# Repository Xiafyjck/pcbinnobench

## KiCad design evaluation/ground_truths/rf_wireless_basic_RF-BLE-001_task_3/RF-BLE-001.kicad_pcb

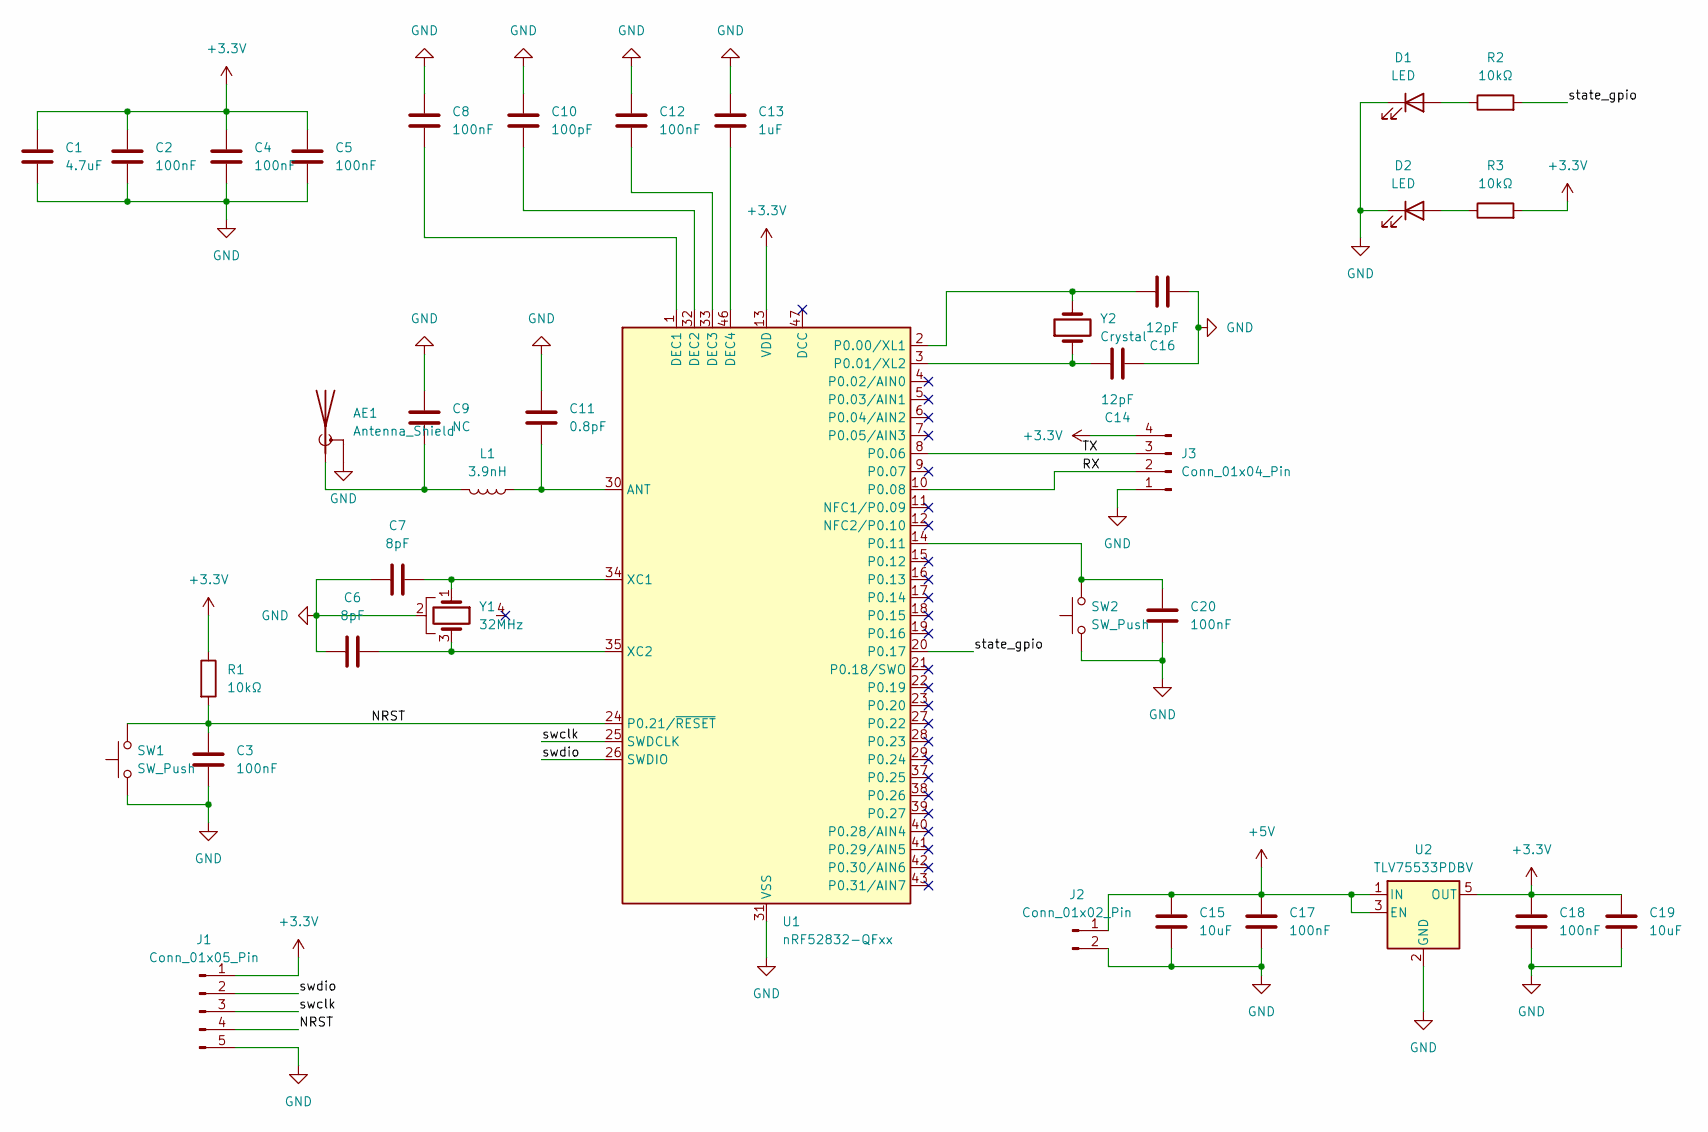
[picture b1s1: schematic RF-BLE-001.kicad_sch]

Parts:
AE1: Antenna_Shield; Texas_SWRA117D_2.4GHz_Right
C1: 4.7uF; C_0805_2012Metric
C2, C3, C4, C5, C8, C12, C17, C18, C20: 100nF; C_0805_2012Metric
C6, C7: 8pF; C_0805_2012Metric
C9: NC; C_0402_1005Metric
C10: 100pF; C_0805_2012Metric
C11: 0.8pF; C_0402_1005Metric
C13: 1uF; C_0805_2012Metric
C14, C16: 12pF; C_0805_2012Metric
C15, C19: 10uF; C_0805_2012Metric
D1, D2: LED; LED_0805_2012Metric
J1: Conn_01x05_Pin; JST_XH_B5B-XH-A_1x05_P2.50mm_Vertical
J2: Conn_01x02_Pin; JST_EH_B2B-EH-A_1x02_P2.50mm_Vertical
J3: Conn_01x04_Pin; JST_XH_B4B-XH-A_1x04_P2.50mm_Vertical
L1: 3.9nH; C_0402_1005Metric
R1, R2, R3: 10kΩ; R_0805_2012Metric
SW1, SW2: SW_Push; SW_PUSH_6mm
U1: nRF52832-QFxx; QFN-48-1EP_6x6mm_P0.4mm_EP4.6x4.6mm
U2: TLV75533PDBV; SOT-23-5
Y1: 32MHz; Crystal_SMD_Abracon_ABM8AIG-4Pin_3.2x2.5mm
Y2: Crystal; Crystal_HC49-4H_Vertical

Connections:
+3.3V: C1.1, C2.1, C4.1, C5.1, C18.1, C19.1, J1.1, J3.4, R1.1, R3.2, U1.13 (VDD), U1.36 (VDD), U1.48 (VDD), U2.5 (OUT)
+5V: C15.1, C17.1, J2.1, U2.1 (IN), U2.3 (EN)
/NRST: C3.1, J1.4, R1.2, SW1.2, U1.24 (P0.21/~RESET)
/RX: J3.2, U1.10 (P0.08)
/TX: J3.3, U1.8 (P0.06)
/state_gpio: R2.2, U1.20 (P0.17)
/swclk: J1.3, U1.25 (SWDCLK)
/swdio: J1.2, U1.26 (SWDIO)
GND: AE1.2 (Shield), C1.2, C2.2, C3.2, C4.2, C5.2, C6.1, C7.1, C8.1, C9.1, C10.1, C11.1, C12.1, C13.1, C14.1, C15.2, C16.1, C17.2, C18.2, C19.2, C20.2, D1.1 (K), D2.1 (K), J1.5, J2.2, J3.1, SW1.1, SW2.1, U1.31 (VSS), U1.45 (VSS), U1.49 (VSS), U2.2 (GND), Y1.2
unnamed: AE1.1 (A), C9.2, L1.2
unnamed: D1.2 (A), R2.1
unnamed: D2.2 (A), R3.1
unnamed: C11.2, L1.1, U1.30 (ANT)
unnamed: C8.2, U1.1 (DEC1)
unnamed: C10.2, U1.32 (DEC2)
unnamed: C12.2, U1.33 (DEC3)
unnamed: C13.2, U1.46 (DEC4)
unnamed: C16.2, U1.2 (P0.00/XL1), Y2.2
unnamed: C14.2, U1.3 (P0.01/XL2), Y2.1
unnamed: C20.1, SW2.2, U1.14 (P0.11)
unnamed: C7.2, U1.34 (XC1), Y1.1
unnamed: C6.2, U1.35 (XC2), Y1.3

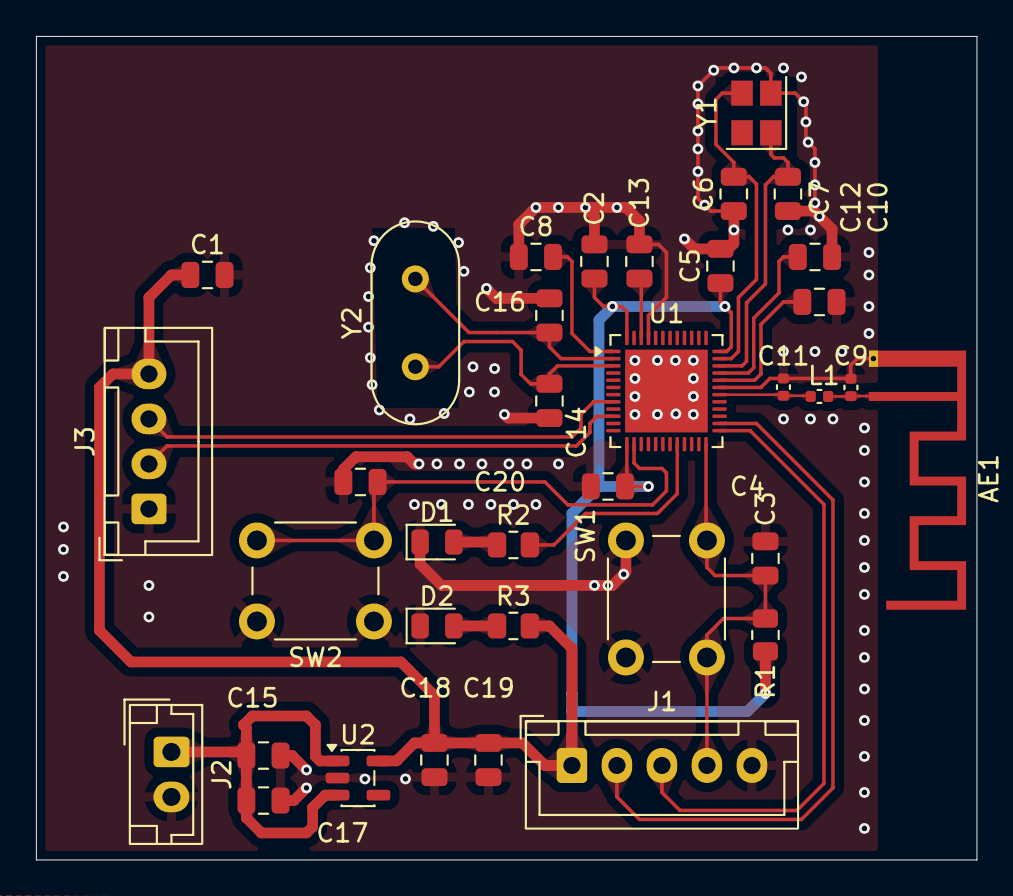
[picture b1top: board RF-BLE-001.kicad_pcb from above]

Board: 4 copper layers, 52.2 x 45.8 mm, 36 parts (0 on the bottom side), 22 nets.

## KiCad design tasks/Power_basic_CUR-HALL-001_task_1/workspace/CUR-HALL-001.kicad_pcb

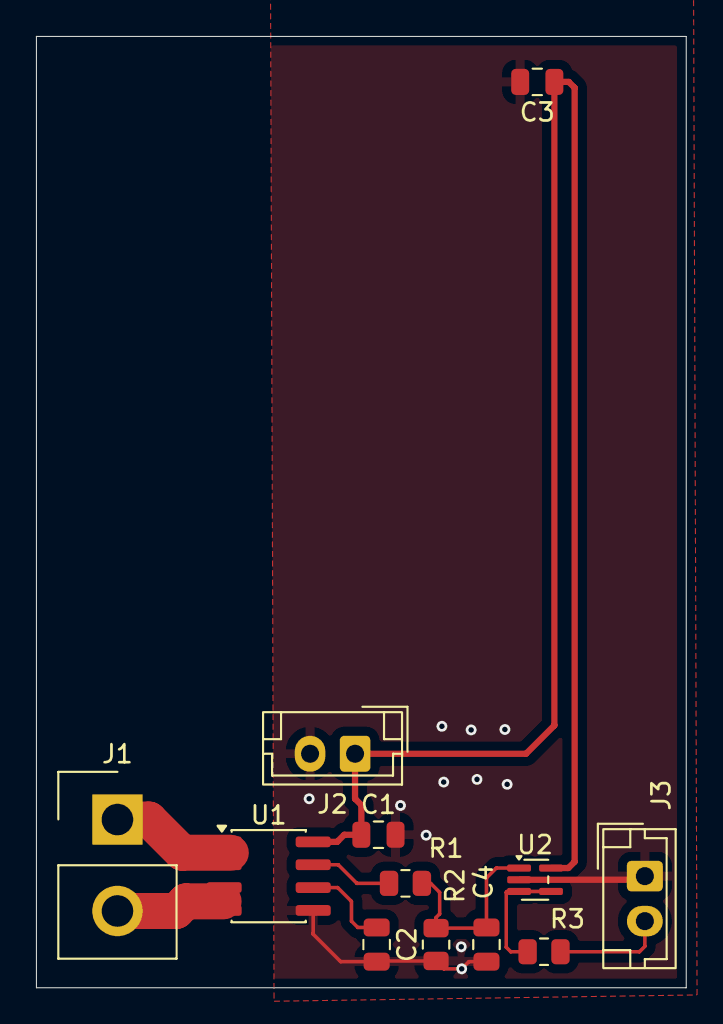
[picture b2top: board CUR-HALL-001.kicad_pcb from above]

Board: 2 copper layers, 36.1 x 52.9 mm, 12 parts (0 on the bottom side), 9 nets.

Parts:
C1, C3: 100nF; C_0805_2012Metric
C2, C4: 10nF; C_0805_2012Metric
J1: Conn_01x02_Pin; Samtec_HPM-02-01-x-S_Straight_1x02_Pitch5.08mm
J2, J3: Conn_01x02_Pin; JST_EH_B2B-EH-A_1x02_P2.50mm_Vertical
R1: 12kΩ; R_0805_2012Metric
R2: 22kΩ; R_0805_2012Metric
R3: 10Ω; R_0805_2012Metric
U1: ACS712xLCTR-20A; SOIC-8_3.9x4.9mm_P1.27mm
U2: OPA333xxDCK; SOT-353_SC-70-5

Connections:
+5V: C1.1, C3.1, J2.1, U1.8 (VCC), U2.5 (V+)
GND: C1.2, C2.2, C3.2, C4.2, J2.2, J3.1, R2.1, U1.5 (GND), U2.2 (V-)
unnamed: J1.1, U1.1 (IP+), U1.2 (IP+)
unnamed: J1.2, U1.3 (IP-), U1.4 (IP-)
unnamed: J3.2, R3.1
unnamed: C2.1, U1.6 (FILTER)
unnamed: R1.1, U1.7 (VIOUT)
unnamed: C4.1, R1.2, R2.2, U2.1 (+)
unnamed: R3.2, U2.3 (-), U2.4

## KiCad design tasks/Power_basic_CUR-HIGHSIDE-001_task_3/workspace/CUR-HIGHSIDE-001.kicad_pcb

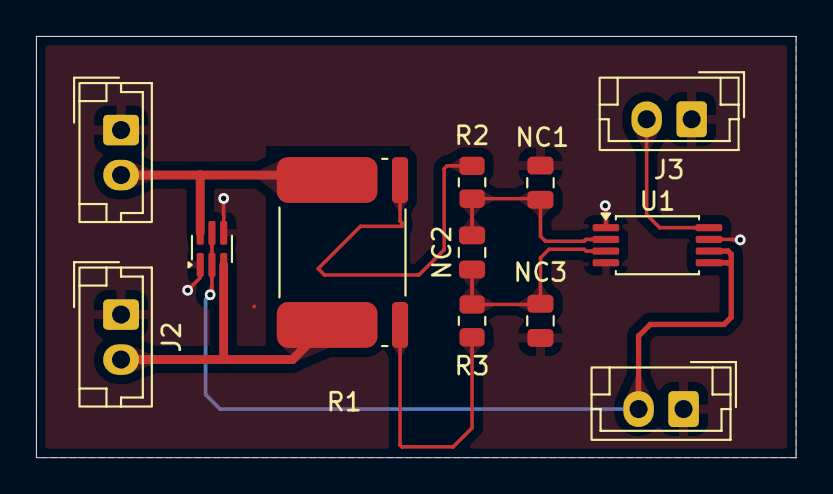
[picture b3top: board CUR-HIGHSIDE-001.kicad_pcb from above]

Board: 2 copper layers, 42.2 x 23.4 mm, 12 parts (0 on the bottom side), 9 nets.

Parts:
D1: BAV199DW; SOT-363_SC-70-6
J1, J2, J3, J4: Conn_01x02_Pin; JST_EH_B2B-EH-A_1x02_P2.50mm_Vertical
NC1: C1; C_0805_2012Metric
NC2: C2; C_0805_2012Metric
NC3: C3; C_0805_2012Metric
R1: 10mΩ; R_Shunt_Isabellenhuette_BVR4026
R2, R3: 0; R_0805_2012Metric
U1: INA240A1PW; TSSOP-8_4.4x3mm_P0.65mm

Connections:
+3V3: D1.2 (K2), D1.5 (K4), J4.2, U1.5 (V+), U1.6 (REF2)
/IN+: D1.6 (K3A4), J1.2, R1.4
/IN-: D1.3 (K1A2), J2.2, R1.1
/OUT: J3.2, U1.8
GND: D1.1 (A1), D1.4 (A3), J1.1, J2.1, J3.1, J4.1, NC1.2, NC3.1, U1.1 (GND), U1.4 (GND), U1.7 (REF1)
unnamed: R1.2, R3.2
unnamed: R1.3, R2.2
unnamed: NC1.1, NC2.2, R2.1, U1.2 (+)
unnamed: NC2.1, NC3.2, R3.1, U1.3 (-)

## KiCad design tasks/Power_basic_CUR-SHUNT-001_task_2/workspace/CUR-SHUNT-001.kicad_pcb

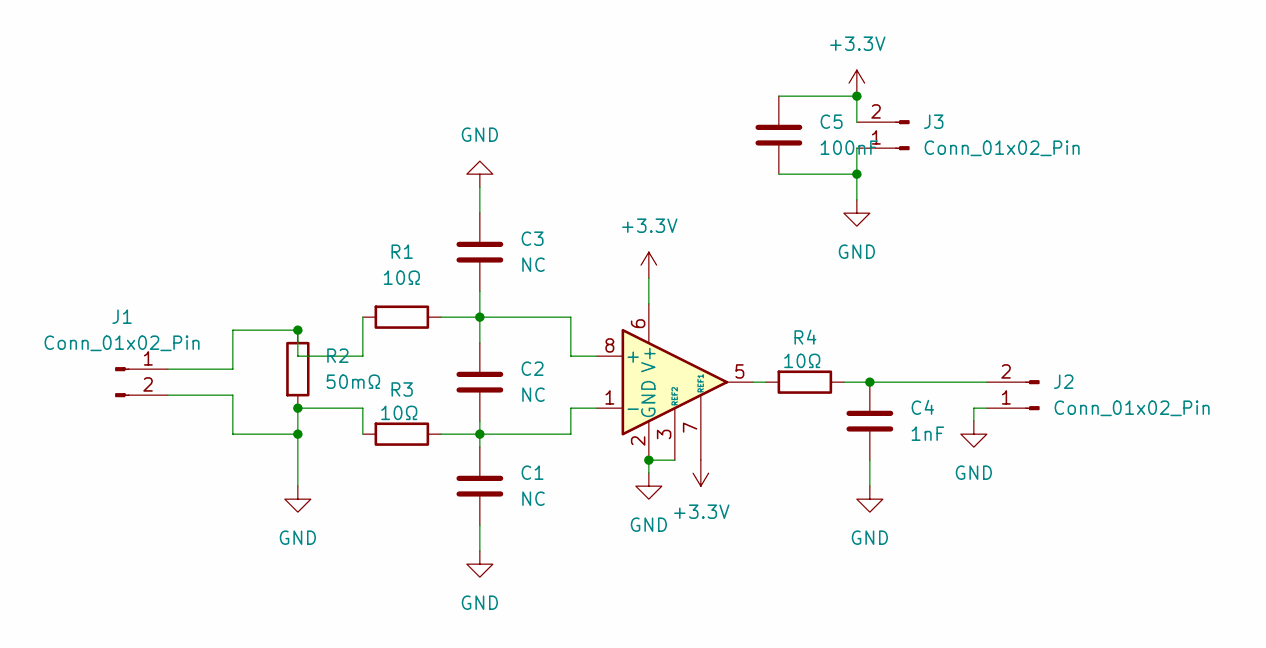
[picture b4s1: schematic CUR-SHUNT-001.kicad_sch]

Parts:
C1, C2, C3: NC; C_0805_2012Metric
C4: 1nF; C_0805_2012Metric
C5: 100nF; C_0805_2012Metric
J1, J2, J3: Conn_01x02_Pin; JST_EH_B2B-EH-A_1x02_P2.50mm_Vertical
R1, R3, R4: 10Ω; R_0805_2012Metric
R2: 50mΩ; R_0603_1608Metric
U2: INA282; SOIC-8_3.9x4.9mm_P1.27mm

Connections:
+3.3V: C5.2, J3.2, U2.6 (V+), U2.7 (REF1)
GND: C1.1, C3.2, C4.1, C5.1, J1.2, J2.1, J3.1, R2.2, R3.2, U2.2 (GND), U2.3 (REF2)
unnamed: J1.1, R1.2, R2.1
unnamed: C4.2, J2.2, R4.1
unnamed: R4.2, U2.5
unnamed: C2.2, C3.1, R1.1, U2.8 (+)
unnamed: C1.2, C2.1, R3.1, U2.1 (-)

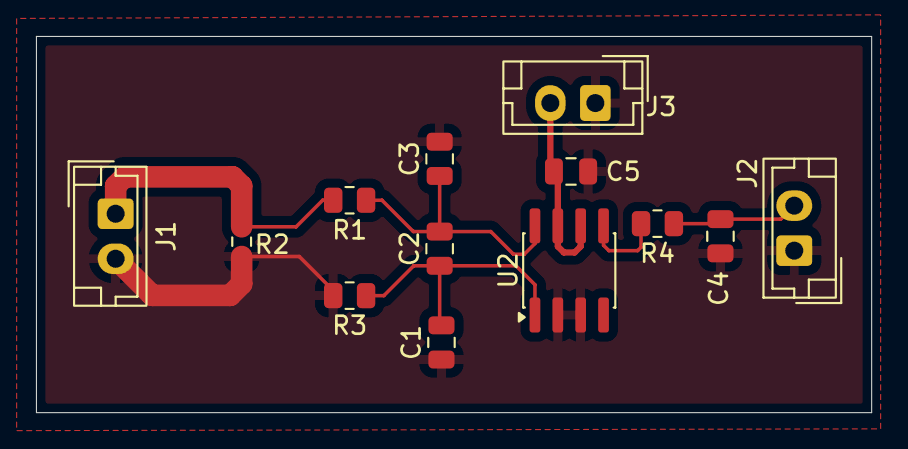
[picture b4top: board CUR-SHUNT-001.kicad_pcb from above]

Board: 2 copper layers, 46.4 x 20.9 mm, 13 parts (0 on the bottom side), 7 nets.

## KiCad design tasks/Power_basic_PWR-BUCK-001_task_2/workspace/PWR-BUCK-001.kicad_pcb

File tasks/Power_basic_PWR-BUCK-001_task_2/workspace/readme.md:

# PWR-BUCK-001

12V to 5V Buck Power Board, used to generate 5V from 12V input.

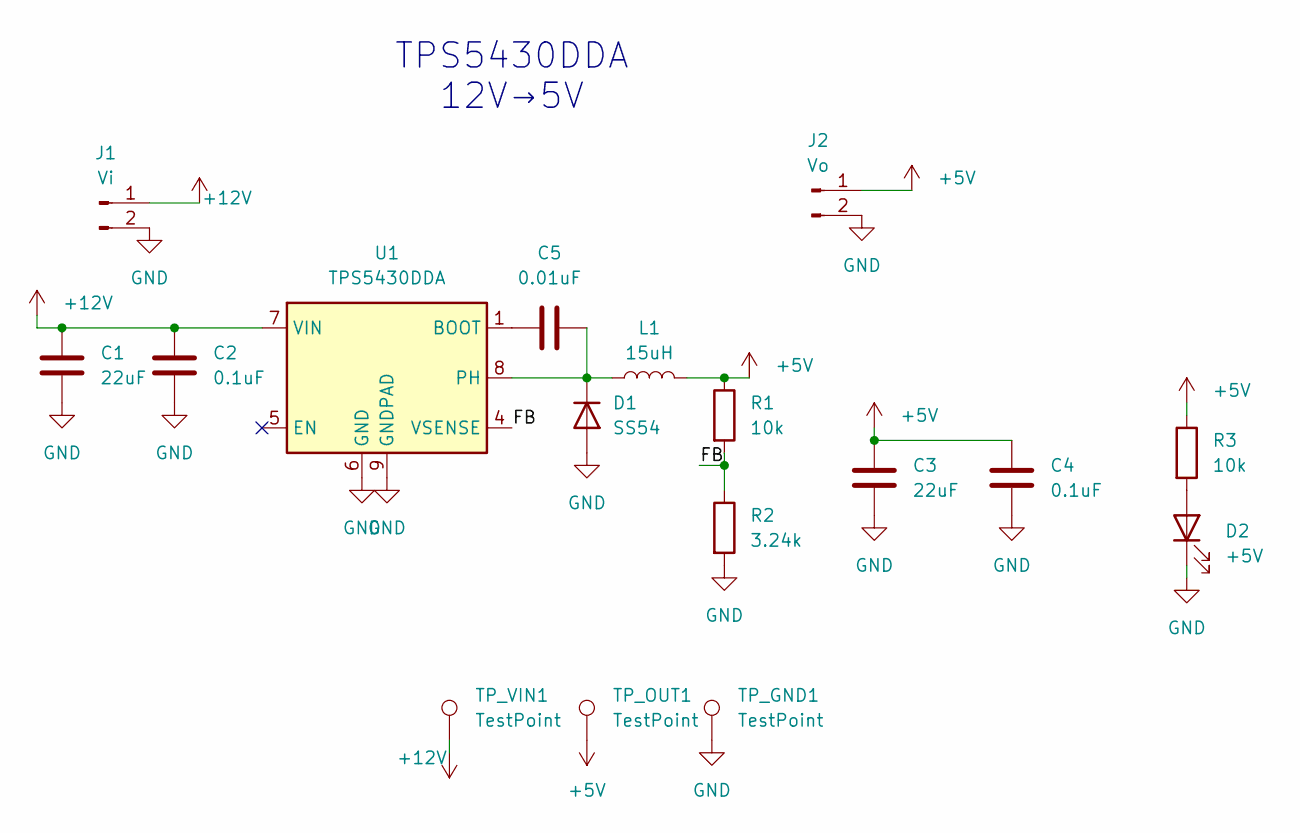
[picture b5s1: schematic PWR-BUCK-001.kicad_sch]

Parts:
C1, C3: 22uF; C_1206_3216Metric
C2, C4: 0.1uF; C_0805_2012Metric
C5: 0.01uF; C_0805_2012Metric
D1: SS54; D_SMB
D2: +5V; LED_0805_2012Metric
J1: Vi; JST_XH_B2B-XH-AM_1x02_P2.50mm_Vertical
J2: Vo; JST_XH_B2B-XH-AM_1x02_P2.50mm_Vertical
L1: 15uH; L_0805_2012Metric
R1, R3: 10k; R_0805_2012Metric
R2: 3.24k; R_0805_2012Metric
TP_GND1: TestPoint; TestPoint_Pad_D2.0mm
TP_OUT1: TestPoint; TestPoint_Pad_D2.0mm
TP_VIN1: TestPoint; TestPoint_Pad_D2.0mm
U1: TPS5430DDA; TI_SO-PowerPAD-8_ThermalVias

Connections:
+5V: C3.1, C4.1, J2.1, L1.2, R1.1, R3.1, TP_OUT1.1
+12V: C1.1, C2.1, J1.1, TP_VIN1.1, U1.7 (VIN)
/FB: R1.2, R2.1, U1.4 (VSENSE)
GND: C1.2, C2.2, C3.2, C4.2, D1.2 (A), D2.1 (K), J1.2, J2.2, R2.2, TP_GND1.1, U1.6 (GND), U1.9 (GNDPAD)
unnamed: C5.2, D1.1 (K), L1.1, U1.8 (PH)
unnamed: D2.2 (A), R3.2
unnamed: C5.1, U1.1 (BOOT)

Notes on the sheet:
TPS5430DDA 12V→5V

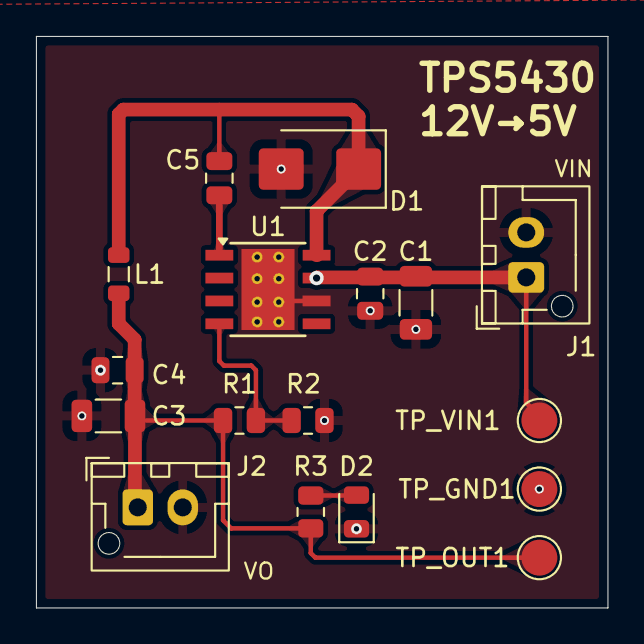
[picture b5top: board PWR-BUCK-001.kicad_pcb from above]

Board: 2 copper layers, 31.8 x 31.8 mm, 17 parts (0 on the bottom side), 7 nets.

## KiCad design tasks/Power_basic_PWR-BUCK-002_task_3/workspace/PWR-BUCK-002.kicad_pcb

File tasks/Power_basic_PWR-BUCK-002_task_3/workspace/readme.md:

# PWR-BUCK-002

Use LM5164 to generate 3.3V control power from industrial 24V input

Switching frequency:

FSW = VOUT × 2500 / R4
     = 3.3 × 2500 / 40
     ≈ 206kHz

Output voltage calculation:

VOUT = 1.2 × (1 + 210k / 120k)
     = 3.3V

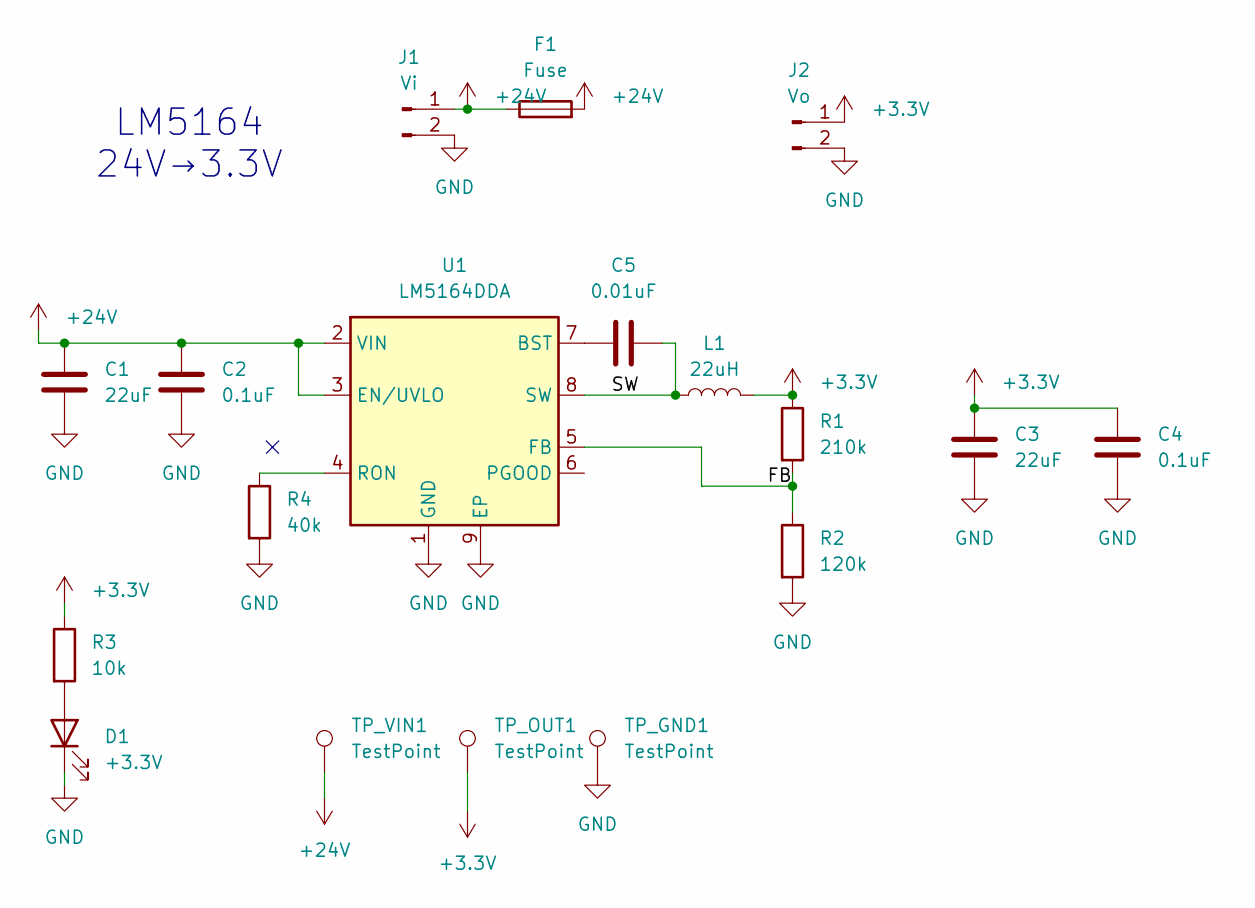
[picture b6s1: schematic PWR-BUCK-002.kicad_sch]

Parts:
C1, C3: 22uF; C_1206_3216Metric
C2, C4: 0.1uF; C_0805_2012Metric
C5: 0.01uF; C_0805_2012Metric
D1: +3.3V; LED_0805_2012Metric
F1: Fuse; Fuse_1210_3225Metric
J1: Vi; JST_XH_B2B-XH-AM_1x02_P2.50mm_Vertical
J2: Vo; JST_XH_B2B-XH-AM_1x02_P2.50mm_Vertical
L1: 22uH; L_6.3x6.3_H3
R1: 210k; R_0805_2012Metric
R2: 120k; R_0805_2012Metric
R3: 10k; R_0805_2012Metric
R4: 40k; R_0805_2012Metric
TP_GND1: TestPoint; TestPoint_Pad_D2.0mm
TP_OUT1: TestPoint; TestPoint_Pad_D2.0mm
TP_VIN1: TestPoint; TestPoint_Pad_D2.0mm
U1: LM5164DDA; HSOP-8-1EP_3.9x4.9mm_P1.27mm_EP2.41x3.1mm_ThermalVias

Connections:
+3.3V: C3.1, C4.1, J2.1, L1.2, R1.1, R3.1, TP_OUT1.1
+24V: C1.1, C2.1, F1.1, F1.2, J1.1, TP_VIN1.1, U1.2 (VIN), U1.3 (EN/UVLO)
/FB: R1.2, R2.1, U1.5 (FB)
/SW: C5.1, L1.1, U1.8 (SW)
GND: C1.2, C2.2, C3.2, C4.2, D1.1 (K), J1.2, J2.2, R2.2, R4.2, TP_GND1.1, U1.1 (GND), U1.9 (EP)
unnamed: D1.2 (A), R3.2
unnamed: C5.2, U1.7 (BST)
unnamed: R4.1, U1.4 (RON)

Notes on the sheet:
LM5164 24V→3.3V

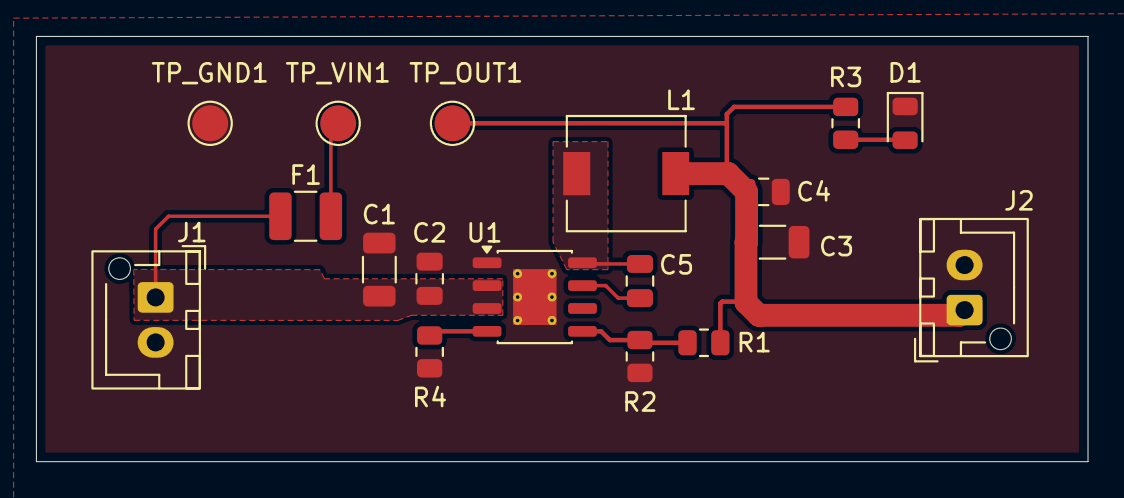
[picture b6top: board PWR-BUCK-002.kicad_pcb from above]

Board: 2 copper layers, 58.4 x 23.6 mm, 18 parts (0 on the bottom side), 8 nets.

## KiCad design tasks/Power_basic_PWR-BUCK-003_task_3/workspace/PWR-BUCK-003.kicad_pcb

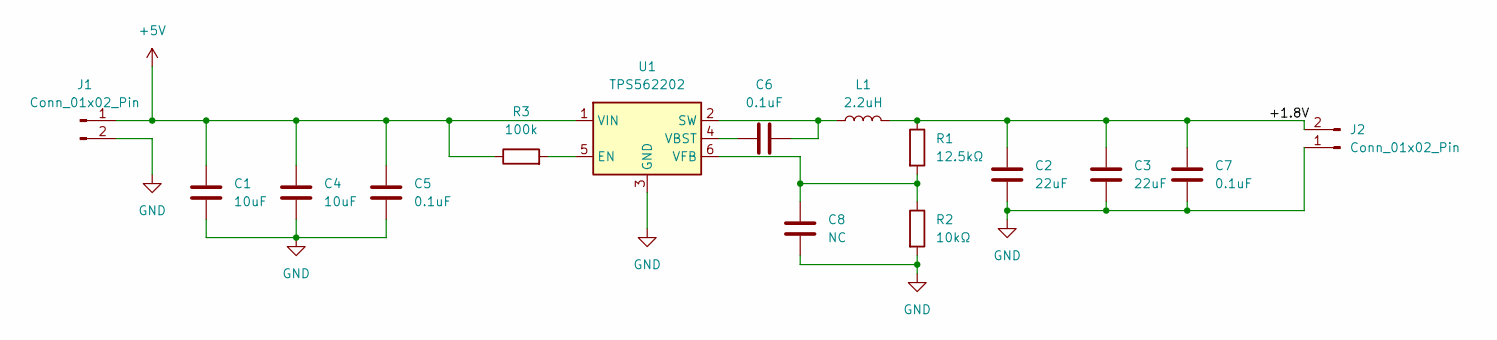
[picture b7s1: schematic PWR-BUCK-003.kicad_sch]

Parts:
C1, C4: 10uF; C_0805_2012Metric
C2, C3: 22uF; C_0201_0603Metric; Rated Voltage 1V
C5, C6: 0.1uF; C_0805_2012Metric
C7: 0.1uF; C_0201_0603Metric; Rated Voltage 1V
C8: NC; C_0805_2012Metric
J1, J2: Conn_01x02_Pin; JST_EH_B2B-EH-A_1x02_P2.50mm_Vertical
L1: 2.2uH; L_10.4x10.4_H4.8
R1: 12.5kΩ; R_0805_2012Metric
R2: 10kΩ; R_0805_2012Metric
R3: 100k; R_0805_2012Metric
U1: TPS562202; SOT-563

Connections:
+5V: C1.1, C4.1, C5.1, J1.1, R3.1, U1.1 (VIN)
/+1.8V: C2.1, C3.1, C7.1, J2.2, L1.2, R1.1
GND: C1.2, C2.2, C3.2, C4.2, C5.2, C7.2, C8.2, J1.2, J2.1, R2.2, U1.3 (GND)
unnamed: R3.2, U1.5 (EN)
unnamed: C6.2, L1.1, U1.2 (SW)
unnamed: C6.1, U1.4 (VBST)
unnamed: C8.1, R1.2, R2.1, U1.6 (VFB)

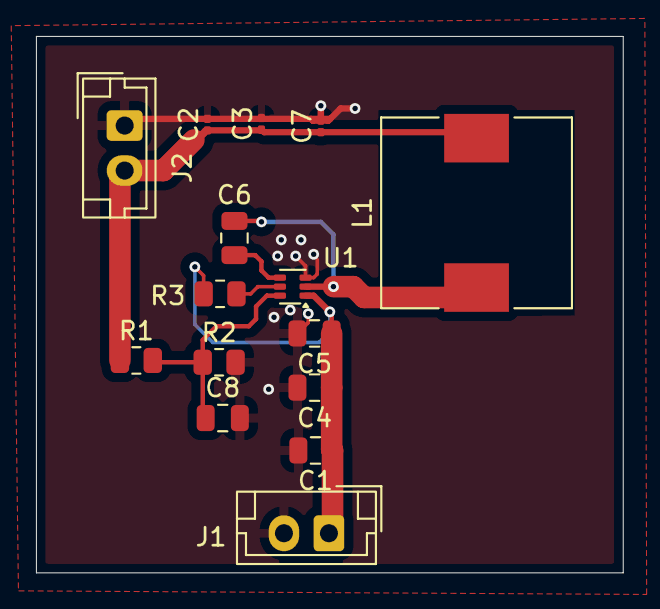
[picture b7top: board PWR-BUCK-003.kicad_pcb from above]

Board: 2 copper layers, 32.6 x 29.8 mm, 15 parts (0 on the bottom side), 7 nets.
